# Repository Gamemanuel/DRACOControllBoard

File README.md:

## Description of my Project:
this is a PCB that i created for my robotics teams t-shirt cannon project. this was my first time using KICAD and i learned alot from making this PCB
## list of materials that i used
RASBERRIE PI PICO x1 i needed USB support and i looked into doing it with transistors but that got complicated fast
Buttons x12 ( i know that i only get 10 so i plan on getting an extra 2 )
LED x6 these are indicator LEDS for when the cannon is ready to fire.
## screenshots
# schematic

# PCB

# 3d model

My slack USERNAME is THEMATHNIGHT

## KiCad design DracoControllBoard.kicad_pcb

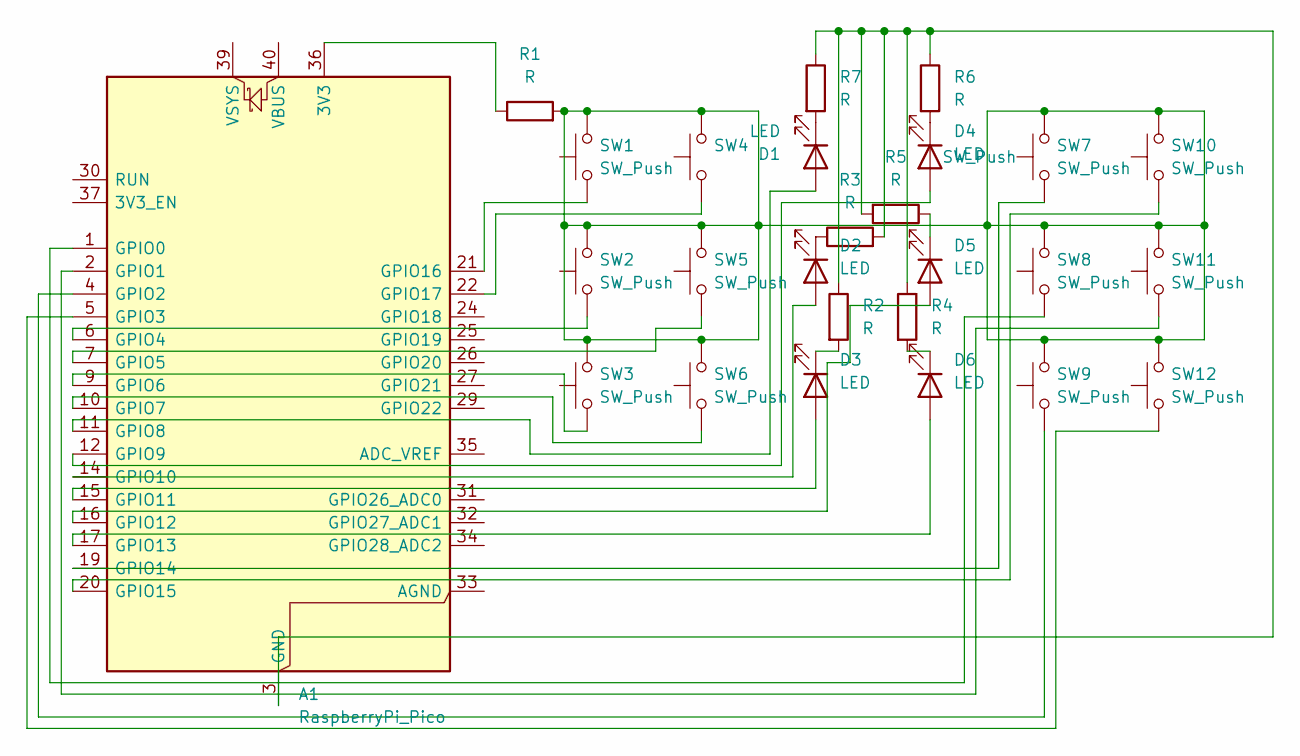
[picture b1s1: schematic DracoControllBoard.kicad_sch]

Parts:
A1: RaspberryPi_Pico; RaspberryPi_Pico_Common_Unspecified
D1, D2, D3, D4, D5, D6: LED; LED_D5.0mm
R1, R2, R3, R4, R5, R6, R7: R; R_Axial_DIN0207_L6.3mm_D2.5mm_P7.62mm_Horizontal
SW1, SW2, SW3, SW4, SW5, SW6, SW7, SW8, SW9, SW10, SW11, SW12: SW_Push; SW_PUSH_6mm

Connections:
unnamed: A1.36 (3V3), R1.1
unnamed: A1.3 (GND), A1.8 (GND), A1.13 (GND), A1.18 (GND), A1.23 (GND), A1.28 (GND), A1.38 (GND), R2.1, R3.2, R4.1, R5.2, R6.1, R7.1
unnamed: A1.1 (GPIO0), SW8.1
unnamed: A1.2 (GPIO1), SW11.1
unnamed: A1.4 (GPIO2), SW9.1
unnamed: A1.5 (GPIO3), SW12.1
unnamed: A1.6 (GPIO4), SW2.1
unnamed: A1.7 (GPIO5), SW5.1
unnamed: A1.9 (GPIO6), SW3.1
unnamed: A1.10 (GPIO7), SW6.1
unnamed: A1.11 (GPIO8), D1.2 (A)
unnamed: A1.12 (GPIO9), D4.2 (A)
unnamed: A1.14 (GPIO10), D2.2 (A)
unnamed: A1.15 (GPIO11), D3.2 (A)
unnamed: A1.16 (GPIO12), D5.2 (A)
unnamed: A1.17 (GPIO13), D6.2 (A)
unnamed: A1.19 (GPIO14), SW7.1
unnamed: A1.20 (GPIO15), SW10.1
unnamed: A1.21 (GPIO16), SW1.1
unnamed: A1.22 (GPIO17), SW4.1
unnamed: D1.1 (K), R7.2
unnamed: D2.1 (K), R3.1
unnamed: D3.1 (K), R2.2
unnamed: D4.1 (K), R6.2
unnamed: D5.1 (K), R5.1
unnamed: D6.1 (K), R4.2
unnamed: R1.2, SW1.2, SW2.2, SW3.2, SW4.2, SW5.2, SW6.2, SW7.2, SW8.2, SW9.2, SW10.2, SW11.2, SW12.2

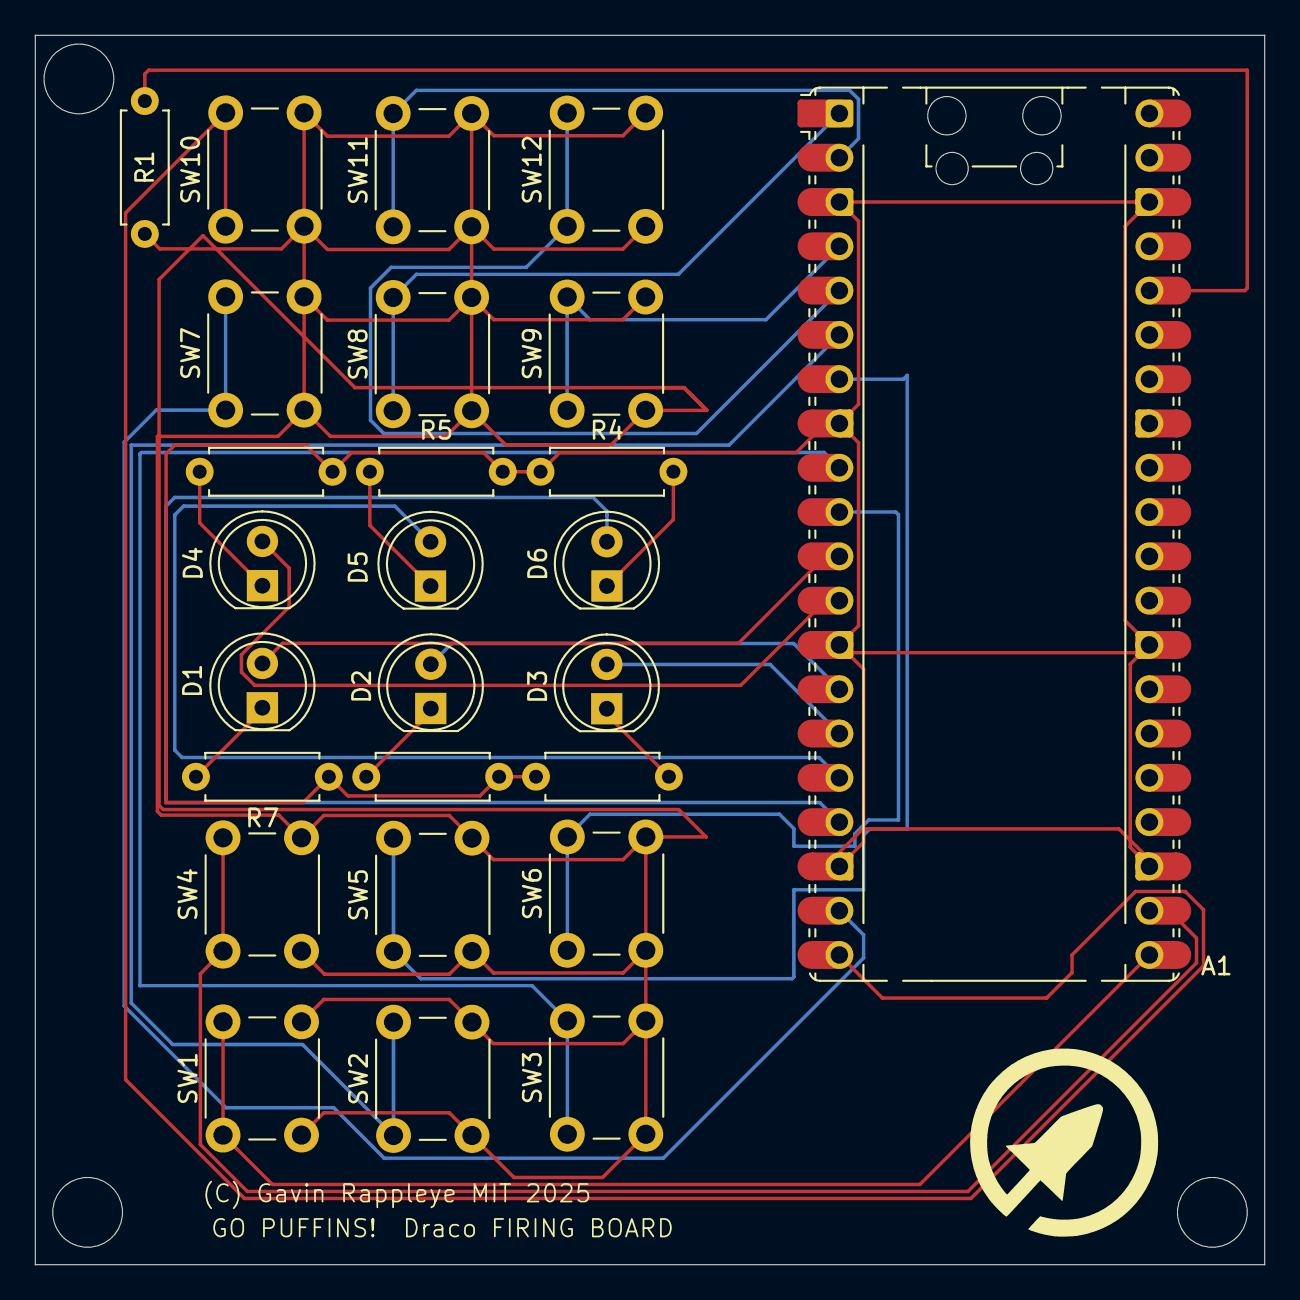
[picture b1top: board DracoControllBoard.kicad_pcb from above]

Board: 2 copper layers, 70.5 x 70.5 mm, 26 parts (0 on the bottom side), 27 nets.

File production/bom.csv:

Designator,Footprint,Quantity,Value,LCSC Part #
A1,RaspberryPi_Pico_Common_Unspecified,1,RaspberryPi_Pico,
"D1, D2, D3, D4, D5, D6",LED_D5.0mm,6,LED,
"R1, R2, R3, R4, R5, R6, R7",R_Axial_DIN0207_L6.3mm_D2.5mm_P7.62mm_Horizontal,7,R,
"SW1, SW10, SW11, SW12, SW2, SW3, SW4, SW5, SW6, SW7, SW8, SW9",SW_PUSH_6mm,12,SW_Push,

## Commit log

2025-05-29 inital commit
2025-05-29 Create LICENSE
2025-05-30 fixted resistor issues
2025-06-01 fixed resistor issue
